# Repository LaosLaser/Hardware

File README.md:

Hardware
========

PCB Designs for the laos project (mainboard)
* 2 - Development version
* rev0.1 - small first series
* rev0.2 - used in various lasers
* rev0.3 - latest version
* rev0.4 - Nr of fixes. Introduced dagerous hardware errors: Grounds disconnected. See wiki!
* rev0.5 - Hardware fixes: routing and ground plane
* rev0.6 - Hardware fix: microSD card holder pinout fixed

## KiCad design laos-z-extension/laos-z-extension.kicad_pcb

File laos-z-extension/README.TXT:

This PCB routes STEP and DIRECTION to 4 pololu's at the same time. It is
used to drive 4 stepper motors on a big Z Frame.

Created by Jaap @ Tuxic.nl, 2015. 

This work falls under the CreativeCommons Attribution-ShareAlike license.
http://creativecommons.org/licenses/by-sa/4.0/

Shortcomings in commit 4bb586817d:

* Pin order of P2 is the opposite of the Pin Order of the output on the
  LaOS board. It would be logical to match those.
* P2 should have an extra pin for ENABLE. It should still be possible to
  use the board without connecting this pin.
* INPUT on P2 could be buffered or seperated with opto coupler for better
  reliability

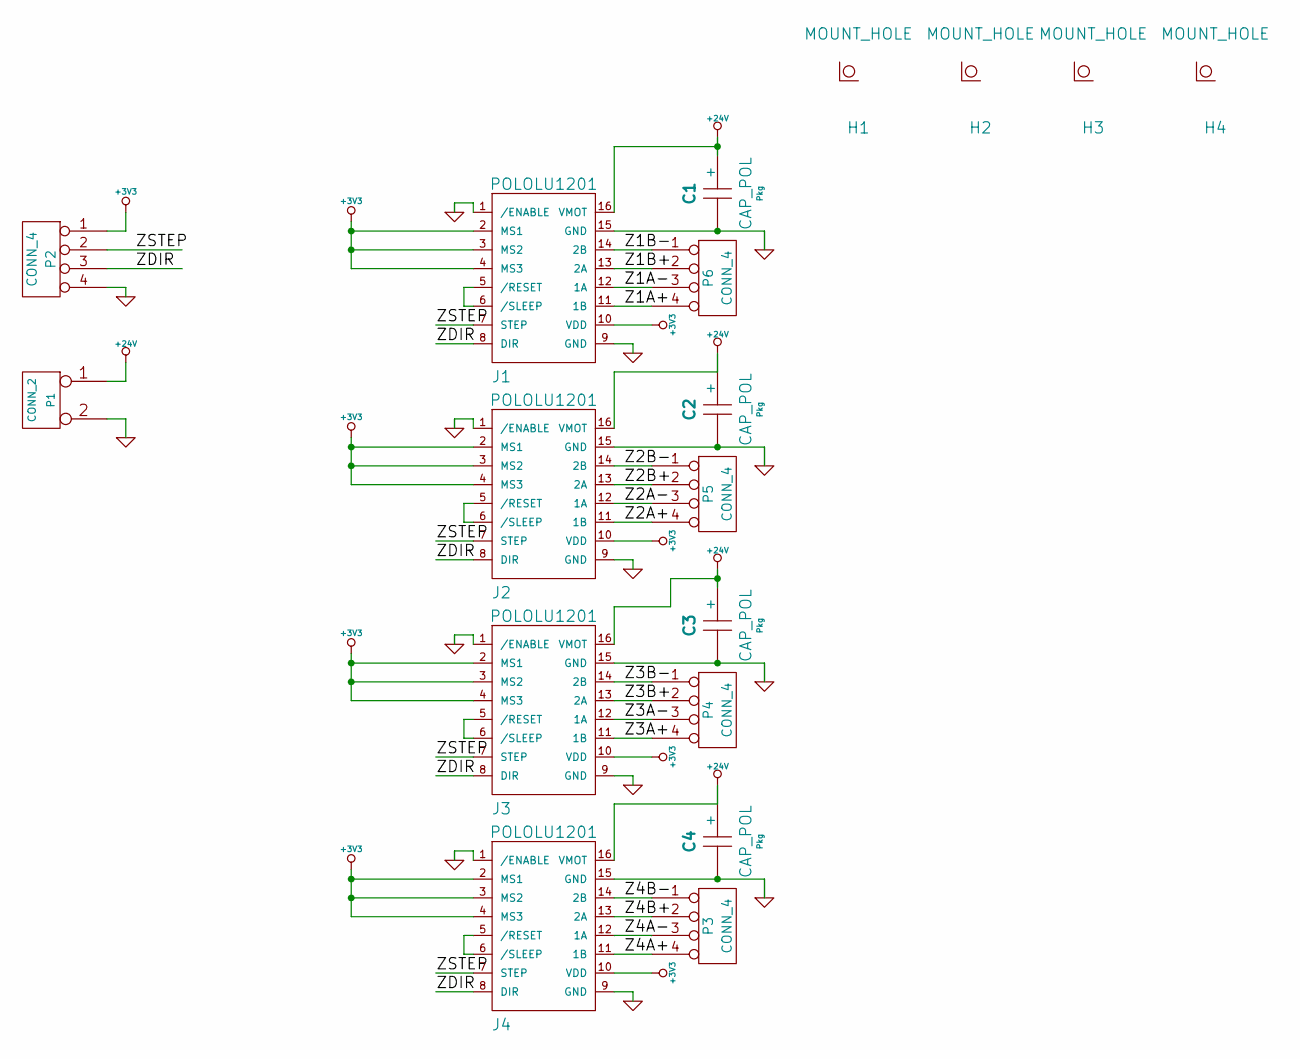
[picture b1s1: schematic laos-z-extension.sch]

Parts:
C1, C2, C3, C4: CAP_POL; Pkg
H1, H2, H3, H4: MOUNT_HOLE
J1, J2, J3, J4: POLOLU1201
P1: CONN_2
P2, P3, P4, P5, P6: CONN_4

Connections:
+3V3: J1.2 (MS1), J1.3 (MS2), J1.4 (MS3), J1.10 (VDD), J2.2 (MS1), J2.3 (MS2), J2.4 (MS3), J2.10 (VDD), J3.2 (MS1), J3.3 (MS2), J3.4 (MS3), J3.10 (VDD), J4.2 (MS1), J4.3 (MS2), J4.4 (MS3), J4.10 (VDD), P2.1
+24V: C1.1 (+), C2.1 (+), C3.1 (+), C4.1 (+), J1.16 (VMOT), J2.16 (VMOT), J3.16 (VMOT), J4.16 (VMOT), P1.1
/Z1A+: J1.11 (1B), P6.4
/Z1A-: J1.12 (1A), P6.3
/Z1B+: J1.13 (2A), P6.2
/Z1B-: J1.14 (2B), P6.1
/Z2A+: J2.11 (1B), P5.4
/Z2A-: J2.12 (1A), P5.3
/Z2B+: J2.13 (2A), P5.2
/Z2B-: J2.14 (2B), P5.1
/Z3A+: J3.11 (1B), P4.4
/Z3A-: J3.12 (1A), P4.3
/Z3B+: J3.13 (2A), P4.2
/Z3B-: J3.14 (2B), P4.1
/Z4A+: J4.11 (1B), P3.4
/Z4A-: J4.12 (1A), P3.3
/Z4B+: J4.13 (2A), P3.2
/Z4B-: J4.14 (2B), P3.1
/ZDIR: J1.8 (DIR), J2.8 (DIR), J3.8 (DIR), J4.8 (DIR), P2.3
/ZSTEP: J1.7 (STEP), J2.7 (STEP), J3.7 (STEP), J4.7 (STEP), P2.2
GND: C1.2, C2.2, C3.2, C4.2, J1.1 (/ENABLE), J1.9 (GND), J1.15 (GND), J2.1 (/ENABLE), J2.9 (GND), J2.15 (GND), J3.1 (/ENABLE), J3.9 (GND), J3.15 (GND), J4.1 (/ENABLE), J4.9 (GND), J4.15 (GND), P1.2 (PM), P2.4
unnamed: J4.5 (/RESET), J4.6 (/SLEEP)
unnamed: J3.5 (/RESET), J3.6 (/SLEEP)
unnamed: J1.5 (/RESET), J1.6 (/SLEEP)
unnamed: J2.5 (/RESET), J2.6 (/SLEEP)

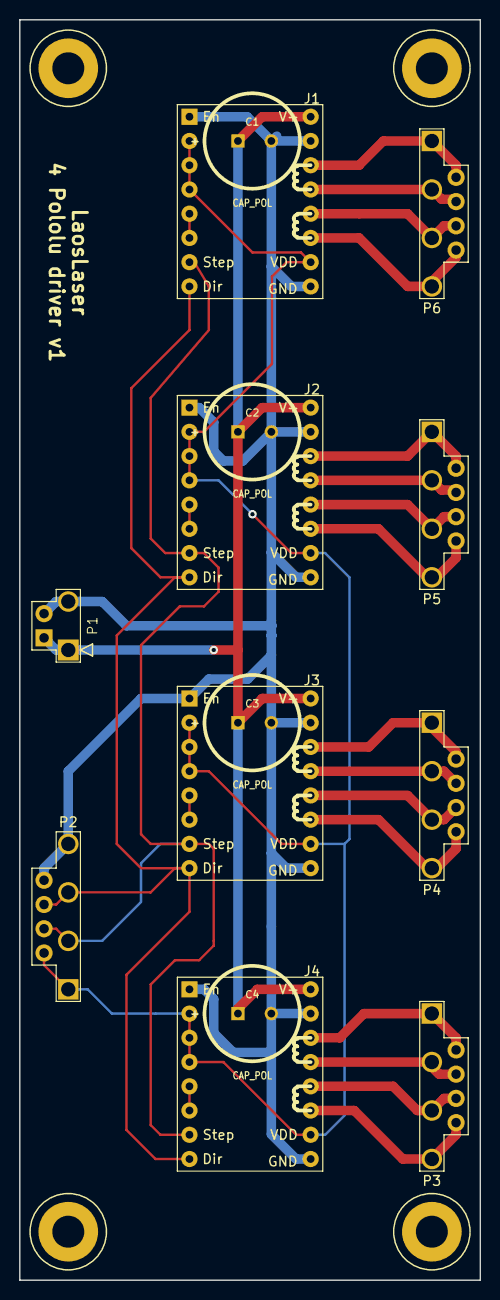
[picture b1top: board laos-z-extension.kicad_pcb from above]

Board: 2 copper layers, 48.3 x 132.1 mm, 18 parts (0 on the bottom side), 25 nets.

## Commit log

2011-01-16 PCB design of controller board
2011-03-08 Added rev1 of the board
2011-03-10 more dataheets, rev2 of board design
2011-04-04 Siert's board (after modifications by Peter)
2011-04-04 renamed
2011-04-04 Added 2.54 connector
2011-06-02 simplified schematics Added info on board layout and connector placement
2011-06-30 Add laos-board revision 2 schematics
2011-07-01 Cleanup and enhancements to match rev 3 laos board
2011-07-01 Add new polulu and some power nets
2011-07-01 Laos board 2 schematic completed before check
2011-07-01 Laos postscript schematic
2011-07-01 Updates before pcb design
2011-07-01 Last minute schematic changes
2011-07-02 Initial work on laos-board footprints
2011-07-06 Initial work on module placement
2011-07-07 More work on module placement for laos-board-2
2011-07-10 More component placement
2011-07-12 Start wiring polulus
2011-07-12 Wiring to the mbed
2011-07-12 Wiring one 4 layers
2011-07-13 More routing work on laos-board-2
2011-07-13 More routing before module compacting
2011-07-14 Update laos-board-2
2011-07-14 Finish 2 layer routing
2011-07-14 Some cleanup
2011-07-14 Board edges jeej
2011-07-14 Final outputs for review laos-board-2
2011-07-14 Add pdf files from postscripts
2011-07-15 Change jumpers near polulus
2011-07-15 Add production files for laos-board v0.1
2011-07-15 Remove silkscreen bottom production file
2011-07-20 eurocircuits production files
2011-09-20 schematic updates to work toward rev.2
2011-09-20 nog een paar wijzigingen van het schema
2011-09-20 Added ethernet PCB modification info for HALO plugs
2011-09-21 Copied the first production-version of the board to a seperate directory. Do not change anythin in laos-board-rev1, as it will never be used again!
2011-09-21 some more rev2 changes
2011-10-15 - Checked schematic - Added connector values and pin text - made pin selection for transistor outputs - Made pull-up resistor values 1K.
2011-10-16 Connect forgotten nets and generate new netlist
2011-10-16 Import new netlist into pcb
2011-10-16 Connect some new nets in the pcb, bad ubuntu
2011-10-16 Connect some new nets in the pcb, and some modules, bad ubuntu
2011-10-16 some more updates to the phoenix connectors
2011-10-17 more board updates...
2011-10-17 connected pin 21 mbed to J41
2011-10-27 Exchange VMOT for VPP because of weird kicad bug
2011-10-27 updated former VMOT net into VPP
2011-10-27 moved text to right places and added comments
2011-10-27 added some more gnd, +5v etc
2011-10-30 Added more text to connectors. Some problems still exist with Vaa / Vpp nets (not connected). and Vin(-) is not connected to GND
2011-10-30 changes after Peter had a look at the board
2011-10-30 connector j5 with 3 wires
2011-10-31 last changes before order? utp
2011-10-31 nog een
2011-10-31 modified pin3 diameter of CONN_3 from 1 to 1.5mm added extra text for jumpers changed track width for Vmot Changed connector orientation Added logo
2011-10-31 Deleted old files
2011-11-25 added pdf of the board
2011-12-15 Removed all outdated output files (Gerbers, PS and PDF) Still need to add new ones, and production files used to order the V2 PCB's
2011-12-15 New rev2 schematics
2012-01-10 svg files for schematic, static rev dir
2012-05-30 new board order (rev0.3) coming up
2012-05-30 forgot to update version number of the schema!
2012-06-02 changes made in Arnhem, ready to go?
2012-06-02 updated J43 to a 3-direction jumper
2012-06-02 added flatcable connector
2012-06-02 renamed pins of flatcable conform official order
2012-06-03 version with swapped usb/network
2012-06-03 cleanup and added texts
2012-06-03 added swap of network/usb to main
2012-06-03 as ordered dd 2012-06-03
2012-06-05 added eurocircuits PCB image
2012-06-05 front image
2012-06-13 corrected location of pdf files for board rev0.2
2012-06-24 schematics
2012-07-09 new PDF file
2012-09-09 Added readme
2012-09-30 first commit for rev4
2012-09-30 added RJ12 for CAN
2012-09-30 added SVG for schematics and board
2012-09-30 updated version numbers to rev4
2012-10-01 updated CAN connector + thicker powerlines
2012-10-01 updated SVGs
2012-10-02 replaced 3v3 voltage regulator, added capacitors for Pololu decoupling
2012-10-05 added gerber files
2012-10-06 smd tryout for rev4
2013-10-26 Update README.md
    Added info on next release of hardware
2013-10-27 Started with new revision, cleaned up the schematic and checked schematic against the old pcb to make sure I didn't break anything
2013-11-10 E-axis removed, pololu default 16x microstepping. Fixes #6
2013-11-10 'Pololu' means Pololu's A4988 drivers, not the DRV882x drivers. Fixes #6
2013-12-23 First functional version, TODO: some polishing and refining
2013-12-23 Resized texts, nice spacing for certain traces, cleaned up track widths
2014-01-01 Last changes and small improvenments
2014-01-02 Micro SD card holder
2014-01-03 Sikscreen texts on back side, output files generated
2014-01-03 Annular ring increased, logo improved
2014-01-05 added pdf schema
2014-01-06 Added Eurocircuits layout PDF
2014-02-19 Fixed O1 and O2 texts, Enlarged holes of J43, clarified text for J43
2014-02-19 Copied connector information to bottom for J5, J9, J18, J24; corrected connector spacing for J10, J14, J27; moved C6
2014-02-19 Gerber files updated
2014-02-19 Save before commit is recommended
2014-02-22 Clarified pinout pololu's; updated production data
2014-02-22 Last changes saved
2014-08-31 MicroSD card holder pinout fixed. Issue from forum, see http://redmine.laoslaser.org/boards/1/topics/689?r=729#message-729 for more information
2014-08-31 Changes saved
2015-02-26 extra board for 4-pololu's on one z-axis
2015-03-08 Added todo list to README
